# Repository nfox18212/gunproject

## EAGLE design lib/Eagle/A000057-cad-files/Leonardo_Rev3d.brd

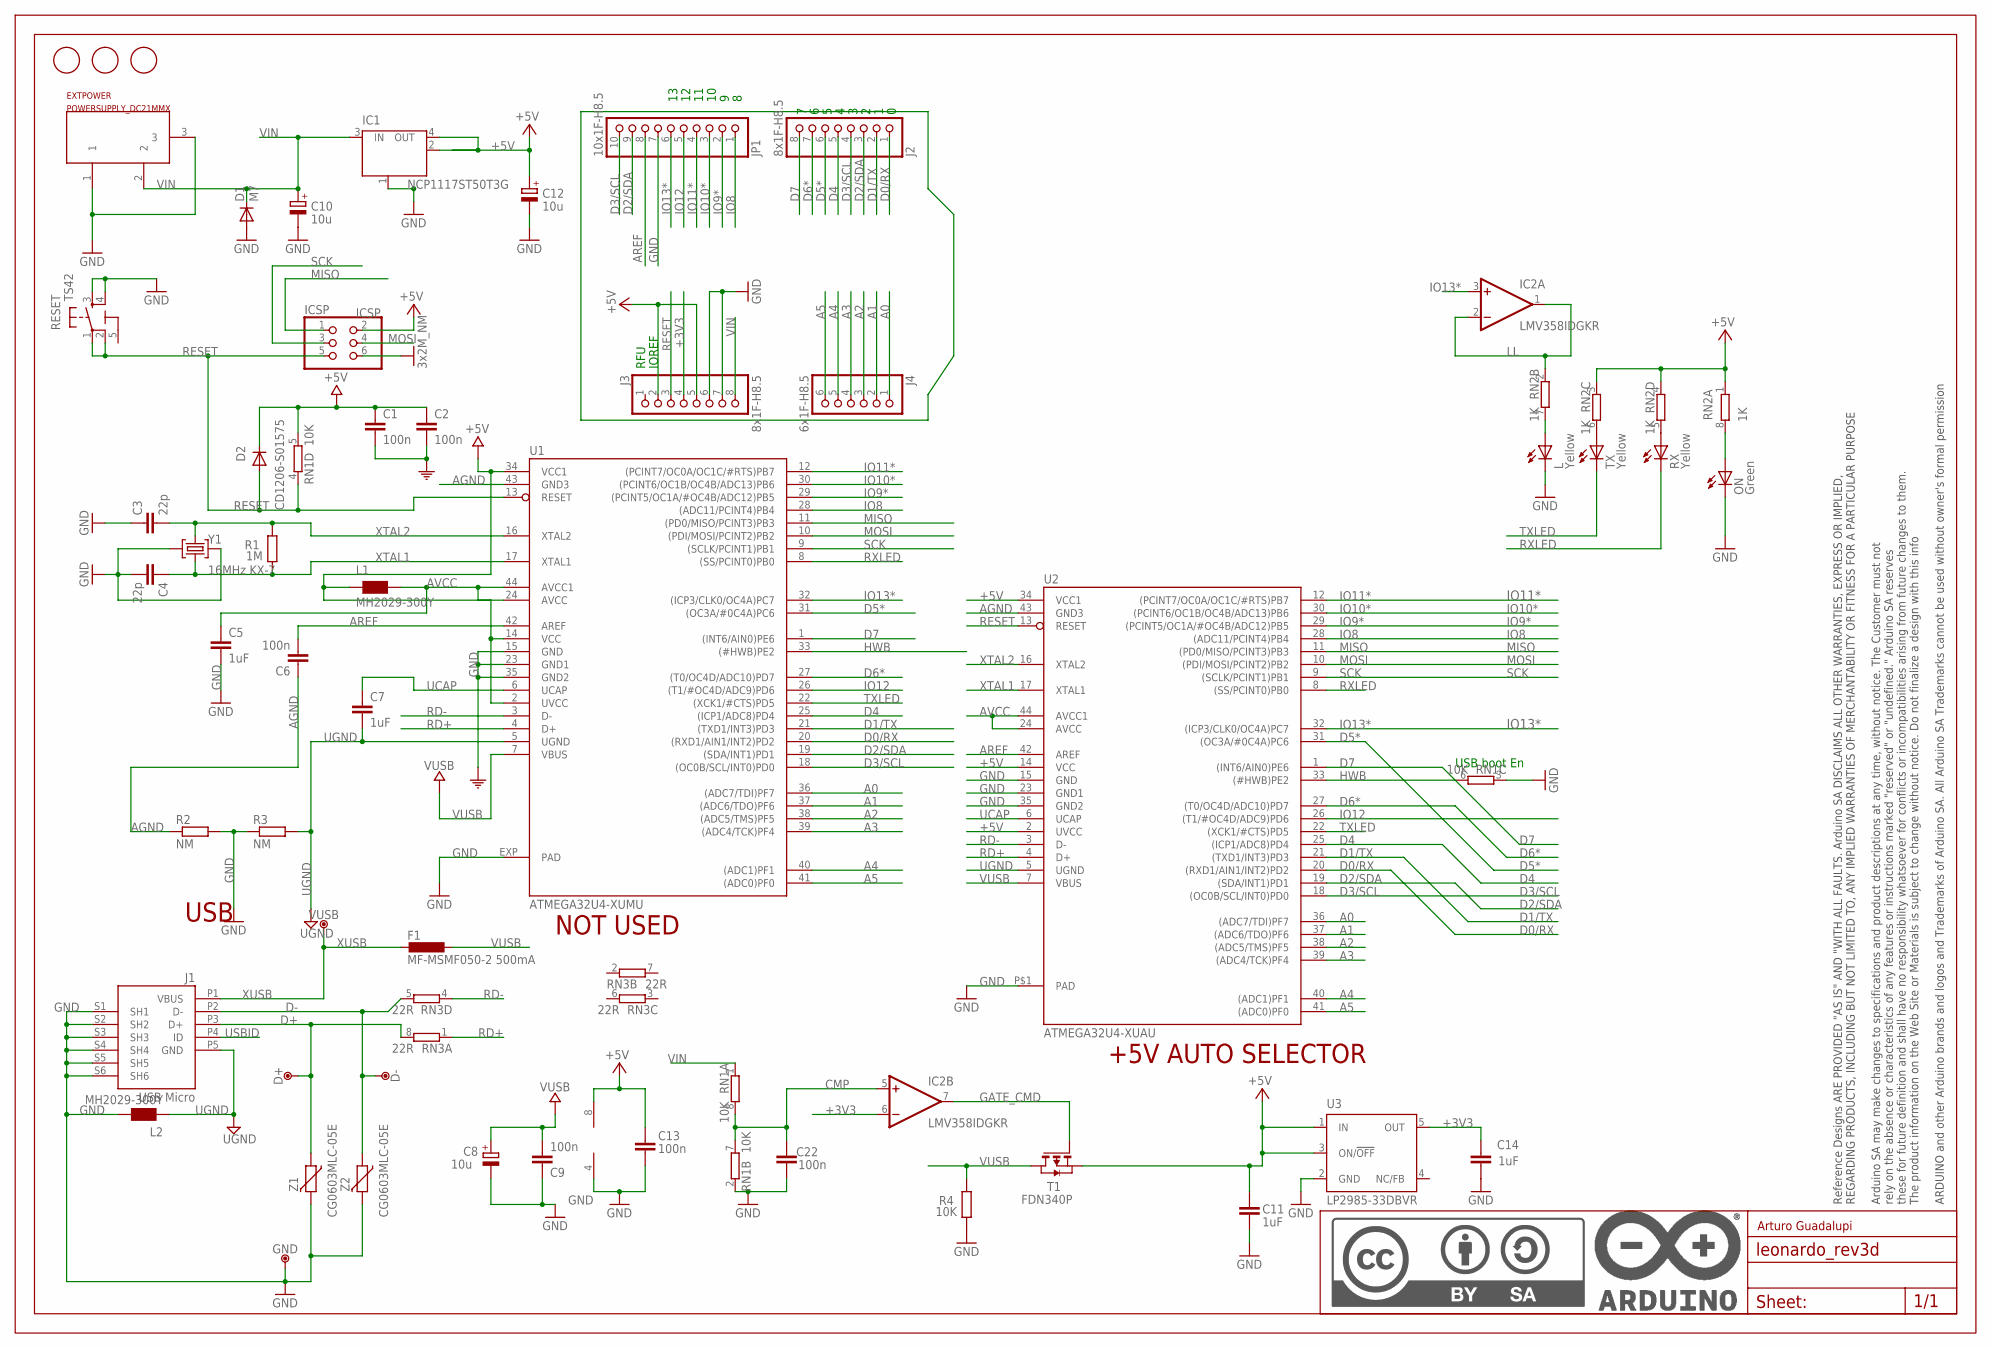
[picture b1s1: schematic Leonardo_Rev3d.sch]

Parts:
C1, C2, C6, C9, C13, C22: 100n; C0603-ROUND
C3, C4: 22p; C0603-ROUND
C5, C7, C11, C14: 1uF; C0603-ROUND
C8, C10, C12: 10u; SMC_B
D1: M7; SMB
D2: CD1206-S01575; MINIMELF
D+: DNP; TP-1.00MM
D-: DNP; TP-1.00MM
EXTPOWER: POWERSUPPLY_DC21MMX; POWERSUPPLY_DC-21MM
F1: MF-MSMF050-2 500mA; L1812
FID1, FID2, FID3: DNP; FD-1-1.5
FRAME1: DNP; FRAME
GND: DNP; TP-1.00MM
IC1: NCP1117ST50T3G; SOT223
IC2: LMV358IDGKR; MSOP08
ICSP: ICSP; 2X03
J1: USB Micro; CON2_USB_MICRO_B_AT
J2, J3: 8x1F-H8.5; 1X08
J4: 6x1F-H8.5; 1X06
JP1: 10x1F-H8.5; 1X10
L: Yellow; CHIPLED_0805
L1, L2: MH2029-300Y; 0805
ON: Green; CHIPLED_0805
R1: 1M; R0603-ROUND
R2, R3: NM; R0402
R4: 10K; R0603-ROUND
RESET: TS42
RN1: 10K; CAY16
RN2: 1K; CAY16
RN3: 22R; CAY16
RX: Yellow; CHIPLED_0805
T1: FDN340P; SOT-23
TX: Yellow; CHIPLED_0805
U1: ATMEGA32U4-XUMU; QFN44ML7X7
U2: ATMEGA32U4-XUAU; TQFP44-PAD
U3: LP2985-33DBVR; SOT23-DBV
VUSB: DNP; TP-1.00MM
Y1: 16MHz KX-7; CRYSTAL-3.2-2.5
Z1, Z2: CG0603MLC-05E; CT/CN0603

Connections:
5-GND: RESET.5 (5-GND)
+3V3: C14.2, IC2.6 (-IN), J3.4, U3.5 (OUT)
+5V: C1.1, C2.1, C11.2, C12.+, C13.1, D2.C, IC1.2 (OUT), IC1.4 (OUT), IC2.8 (V+), ICSP.2, J3.2, J3.5, L1.1, RN1.5 (2), RN2.1, RN2.3 (1), RN2.4 (1), T1.2 (S), U1.2 (UVCC), U1.14 (VCC), U1.34 (VCC1), U2.2 (UVCC), U2.14 (VCC), U2.34 (VCC1), U3.1 (IN), U3.3 (ON/!OFF)
A0: J4.1, U1.36 ((ADC7/TDI)PF7), U2.36 ((ADC7/TDI)PF7)
A1: J4.2, U1.37 ((ADC6/TDO)PF6), U2.37 ((ADC6/TDO)PF6)
A2: J4.3, U1.38 ((ADC5/TMS)PF5), U2.38 ((ADC5/TMS)PF5)
A3: J4.4, U1.39 ((ADC4/TCK)PF4), U2.39 ((ADC4/TCK)PF4)
A4: J4.5, U1.40 ((ADC1)PF1), U2.40 ((ADC1)PF1)
A5: J4.6, U1.41 ((ADC0)PF0), U2.41 ((ADC0)PF0)
AGND: C6.1, R2.1, U1.43 (GND3), U2.43 (GND3)
AREF: C6.2, JP1.8, U1.42 (AREF), U2.42 (AREF)
AVCC: C5.1, L1.2, U1.24 (AVCC), U1.44 (AVCC1), U2.24 (AVCC), U2.44 (AVCC1)
CMP: C22.2, IC2.5 (+IN), RN1.7 (2), RN1.8 (2)
D0/RX: J2.1, U1.20 ((RXD1/AIN1/INT2)PD2), U2.20 ((RXD1/AIN1/INT2)PD2)
D1/TX: J2.2, U1.21 ((TXD1/INT3)PD3), U2.21 ((TXD1/INT3)PD3)
D2/SDA: J2.3, JP1.9, U1.19 ((SDA/INT1)PD1), U2.19 ((SDA/INT1)PD1)
D3/SCL: J2.4, JP1.10, U1.18 ((OC0B/SCL/INT0)PD0), U2.18 ((OC0B/SCL/INT0)PD0)
D4: J2.5, U1.25 ((ICP1/ADC8)PD4), U2.25 ((ICP1/ADC8)PD4)
D5*: J2.6, U1.31 ((OC3A/#0C4A)PC6), U2.31 ((OC3A/#0C4A)PC6)
D6*: J2.7, U1.27 ((T0/OC4D/ADC10)PD7), U2.27 ((T0/OC4D/ADC10)PD7)
D7: J2.8, U1.1 ((INT6/AIN0)PE6), U2.1 ((INT6/AIN0)PE6)
D+: D+.X, J1.P3 (D+), RN3.8 (2), Z1.1
D-: D-.X, J1.P2 (D-), RN3.5 (2), Z2.1
GATE_CMD: IC2.7 (OUT), T1.3 (G)
GND: C1.2, C2.2, C3.1, C4.2, C5.2, C8.-, C9.1, C10.-, C11.1, C12.-, C13.2, C14.1, C22.1, D1.A, EXTPOWER.1, EXTPOWER.3, GND.X, IC1.1 (GND/ADJ), IC2.4 (V-), ICSP.6, J1.S1 (SH1), J1.S2 (SH2), J1.S3 (SH3), J1.S4 (SH4), J1.S5 (SH5), J1.S6 (SH6), J3.6, J3.7, JP1.7, L.C, L2.2, ON.C, R2.2, R3.1, R4.1, RESET.3, RESET.4, RN1.2 (1), RN1.3 (1), U1.15 (GND), U1.23 (GND1), U1.35 (GND2), U1.EXP (PAD), U2.15 (GND), U2.23 (GND1), U2.35 (GND2), U2.P$1 (PAD), U3.2 (GND), Y1.2 (GND), Y1.4 (GND), Z1.2, Z2.2
HWB: RN1.6 (2), U1.33 ((#HWB)PE2), U2.33 ((#HWB)PE2)
IO8: JP1.1, U1.28 ((ADC11/PCINT4)PB4), U2.28 ((ADC11/PCINT4)PB4)
IO9*: JP1.2, U1.29 ((PCINT5/OC1A/#OC4B/ADC12)PB5), U2.29 ((PCINT5/OC1A/#OC4B/ADC12)PB5)
IO10*: JP1.3, U1.30 ((PCINT6/OC1B/OC4B/ADC13)PB6), U2.30 ((PCINT6/OC1B/OC4B/ADC13)PB6)
IO11*: JP1.4, U1.12 ((PCINT7/OC0A/OC1C/#RTS)PB7), U2.12 ((PCINT7/OC0A/OC1C/#RTS)PB7)
IO12: JP1.5, U1.26 ((T1/#OC4D/ADC9)PD6), U2.26 ((T1/#OC4D/ADC9)PD6)
IO13*: IC2.3 (+IN), JP1.6, U1.32 ((ICP3/CLK0/OC4A)PC7), U2.32 ((ICP3/CLK0/OC4A)PC7)
LL: IC2.1 (OUT), IC2.2 (-IN), RN2.2 (1)
MISO: ICSP.1, U1.11 ((PD0/MISO/PCINT3)PB3), U2.11 ((PD0/MISO/PCINT3)PB3)
MOSI: ICSP.4, U1.10 ((PDI/MOSI/PCINT2)PB2), U2.10 ((PDI/MOSI/PCINT2)PB2)
unnamed: L.A, RN2.7 (2)
unnamed: ON.A, RN2.8 (2)
unnamed: RN2.6 (2), TX.A
unnamed: RN2.5 (2), RX.A
RD+: RN3.1, U1.4 (D+), U2.4 (D+)
RD-: RN3.4 (1), U1.3 (D-), U2.3 (D-)
RESET: D2.A, ICSP.5, J3.3, RESET.1, RESET.2, RN1.4 (1), U1.13 (RESET), U2.13 (RESET)
RXLED: RX.C, U1.8 ((SS/PCINT0)PB0), U2.8 ((SS/PCINT0)PB0)
SCK: ICSP.3, U1.9 ((SCLK/PCINT1)PB1), U2.9 ((SCLK/PCINT1)PB1)
TXLED: TX.C, U1.22 ((XCK1/#CTS)PD5), U2.22 ((XCK1/#CTS)PD5)
UCAP: C7.1, U1.6 (UCAP), U2.6 (UCAP)
UGND: C7.2, J1.P5 (GND), L2.1, R3.2, U1.5 (UGND), U2.5 (UGND)
USBID: J1.P4 (ID)
VIN: C10.+, D1.C, EXTPOWER.2, IC1.3 (IN), J3.8, RN1.1
VUSB: C8.+, C9.2, F1.1, R4.2, T1.1 (D), U1.7 (VBUS), U2.7 (VBUS)
XTAL1: C4.1, R1.1, U1.17 (XTAL1), U2.17 (XTAL1), Y1.1 (C1)
XTAL2: C3.2, R1.2, U1.16 (XTAL2), U2.16 (XTAL2), Y1.3 (C2)
XUSB: F1.2, J1.P1 (VBUS), VUSB.X

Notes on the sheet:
USB boot En
USB
+5V AUTO SELECTOR
NOT USED
IOREF
RFU
Arturo Guadalupi

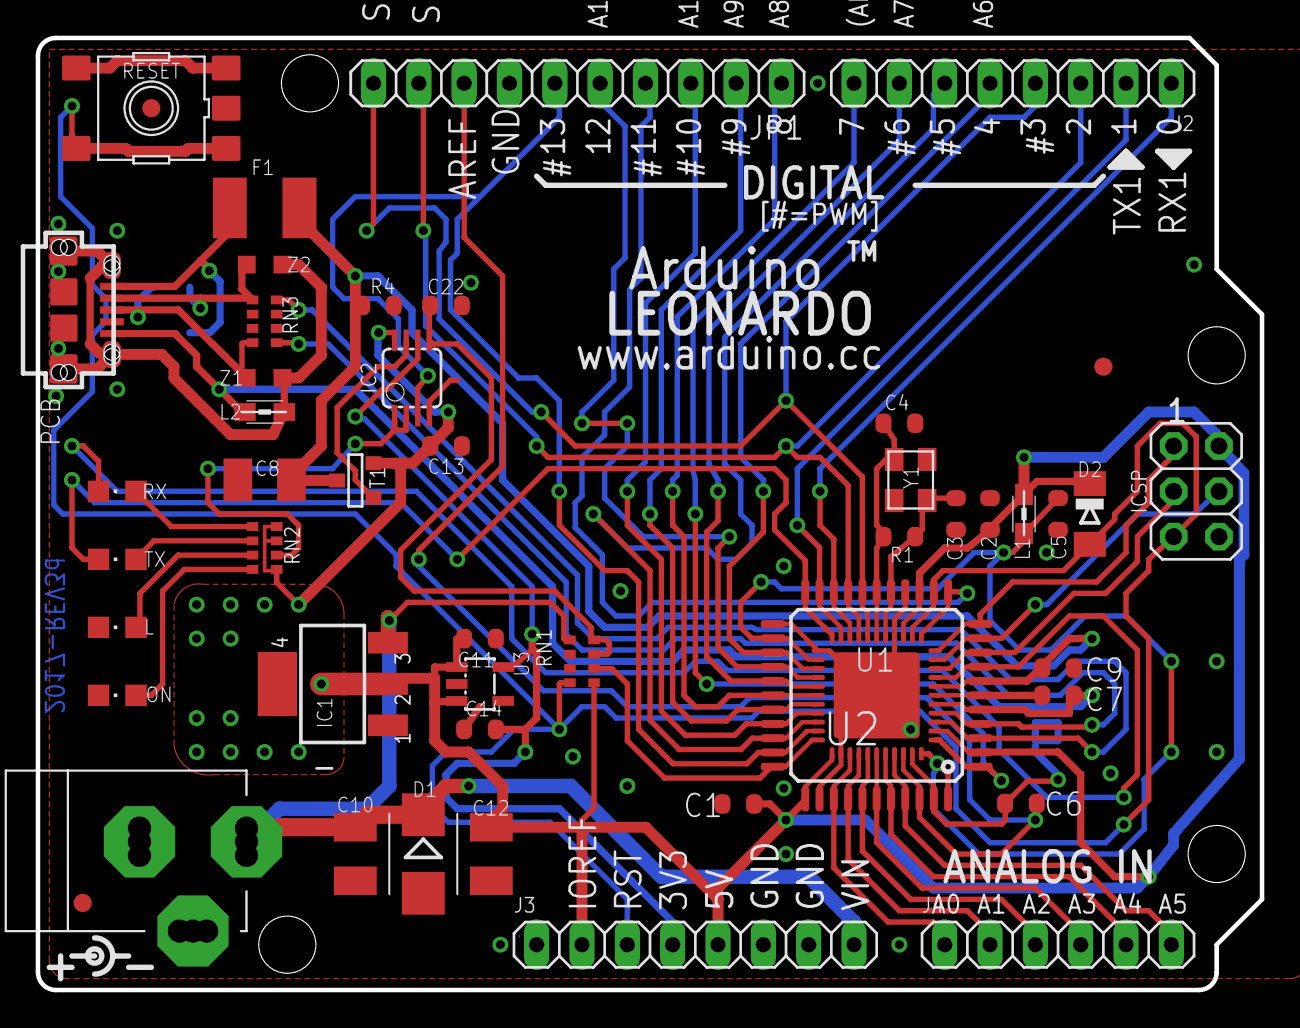
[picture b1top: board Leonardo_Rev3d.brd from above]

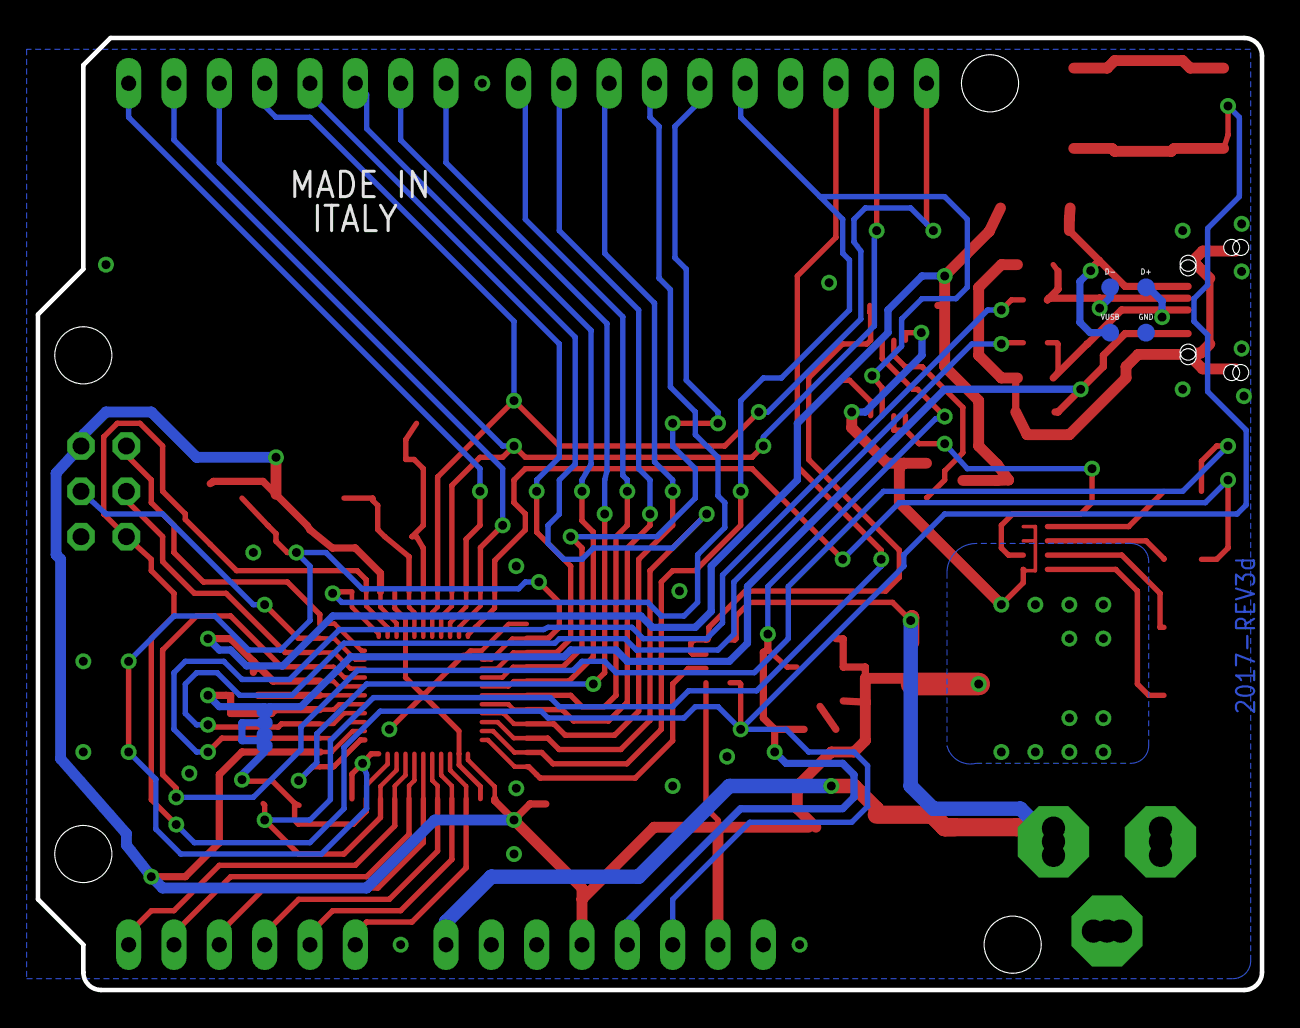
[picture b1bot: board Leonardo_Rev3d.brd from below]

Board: 2 copper layers, 68.6 x 53.3 mm, 56 parts (2 on the bottom side), 51 nets.

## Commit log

2024-10-04 Init project
2024-10-28 refactor
2024-10-29 changed project structure
2024-10-29 started platform.io project and added eagle schematics for library
2024-10-30 added accelerometer mouse prototype
2024-10-30 added kicad schematics for load cell and arduino
2024-11-01 added kicad stuff
2024-11-04 updated schematics; updated hk711 symbol
2024-11-07 deleted a couple files
2024-11-11 added submodule and ddr stuff, moving to fsr instead of load sensor
2024-11-11 updated .gitignore
2024-11-11 updated fsr
2024-11-11 worked on schematic in lecture
2024-11-12 updated movement pad
2024-11-13 tinkered with top level pad, add in i2c chip?
2024-11-15 added LEDs
2024-11-15 Added gamedev.drawio
2024-11-15 Added pad project and edited pad schematic
2024-11-18 realized i screwed up with movement pad, redid it
2024-11-18 Reworked pad schematic again because the hookup guides are annoying
2024-11-18 Added docs dir
2024-11-18 HerbsUpdate gamedev.drawio
2024-11-18 New changes gamedev.drawio
2024-11-18 NewUpdate gamedev.drawio
2024-11-20 added schematic for gun controller
2024-11-20 Changed SCL wire color and added trigger buttons
2024-11-20 Changed arcade push button wire color
2024-11-20 Re-added herb's diagrams
2024-11-20 Re-added Docs dir
2024-11-22 Fixed accelerometer not being connected to i2c in schematic
2024-11-22 started making inventor parts
2024-11-25 worked on box/grip
2024-11-25 modified project file
2024-12-06 updated inventor project after aeons
2024-12-10 maybe removing git-lfs will fix the inventor corruption
2024-12-11 push
2024-12-11 it fucking works
2024-12-11 box edit
2024-12-11 added body pipe
2024-12-11 bringbacklib
2024-12-11 Revert "added body pipe"
    This reverts commit d8ffdef557ddd8e62bafe0f231c1672d28b3c69d.
2024-12-12 finished initial gun model
2024-12-18 Changed accelerometer to BNO055 changed Arcade button wires
2024-12-19 added panel, base, and movement pad parts
2025-01-23 changes from last semester design doc submission
2025-02-03 added button code
2025-02-05 start screwing around with arduino, need to do more work cuz i was lazy
2025-02-05 fixed platformio.ini file
2025-02-07 new2
2025-02-07 started adding keyboard combos and structure of project
2025-02-17 update sending keyboard input
2025-02-23 minor work
2025-02-24 started writing new function for reading analogue pins
2025-02-26 debugging is hard
2025-02-26 arduino interrupts make no sense
2025-02-27 augh
2025-02-28 found the bug in updateState and did more research into simavr
2025-03-24 serial no longer works
2025-03-25 finished algorithm for one FSR
2025-03-25 somehow accidentally deleted sendKey and switch in last commit
2025-03-26 added some docs
2025-03-26 finished switch main statement
2025-03-31 finished code
2025-04-21 added logs from initial testing, added more debugging code
2025-04-26 added a ton of data
2025-05-07 data lots of data
2025-05-07 added image
2025-05-11 updated schematic

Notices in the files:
lib/Eagle/A000057-cad-files/Leonardo_Rev3d.brd:
Copyright (c) 2016-2017 Arduino LLC.  All right reserved. EAGLE Design Rules
parts and their libraries:
Arduino-utility: Copyright (c) 2016-2017 Arduino LLC.  All right reserved.
